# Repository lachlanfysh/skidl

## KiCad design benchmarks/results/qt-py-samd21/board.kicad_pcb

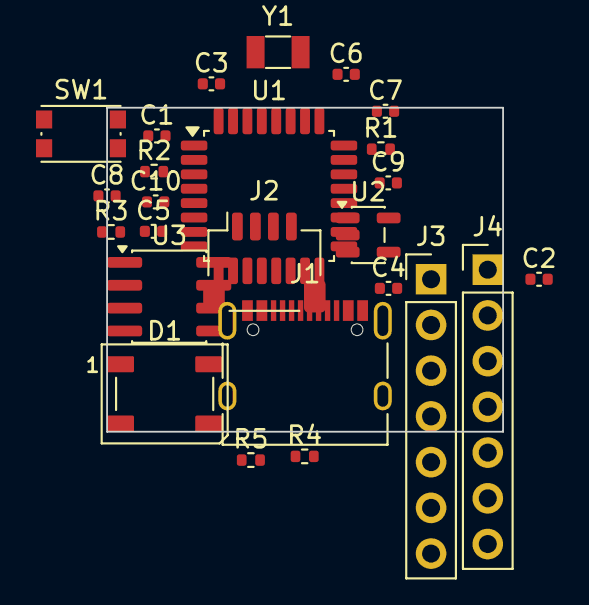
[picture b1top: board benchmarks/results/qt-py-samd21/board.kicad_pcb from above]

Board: 2 copper layers, 22.0 x 18.0 mm, 25 parts (0 on the bottom side), 25 nets, no tracks yet.

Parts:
C1, C2, C3: 1uF; C_0402_1005Metric
C4, C5, C8, C9, C10: 100nF; C_0402_1005Metric
C6, C7: 6.8pF; C_0402_1005Metric
D1: WS2812B; LED_WS2812B_PLCC4_5.0x5.0mm_P3.2mm
J1: USB_C; USB_C_Receptacle_XKB_U262-16XN-4BVC11
J2: Conn_01x04; JST_SH_SM04B-SRSS-TB_1x04-1MP_P1.00mm_Horizontal
J3, J4: Conn_01x07; PinHeader_1x07_P2.54mm_Vertical
R1, R2: 5.1K; R_0402_1005Metric
R3, R4, R5: 10K; R_0402_1005Metric
SW1: SW_Push; SW_Push_1P1T_NO_CK_KMR2
U1: ATSAMD21E18A-A; TQFP-32_7x7mm_P0.8mm
U2: AP2112K-3.3; SOT-23-5
U3: GD25Q16; SOIC-8_3.9x4.9mm_P1.27mm
Y1: 32.768kHz; Crystal_SMD_3215-2Pin_3.2x1.5mm

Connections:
+3V3: C2.1, C4.1, C5.1, C9.1, C10.1, D1.1, J2.2, J3.1, R3.1, R4.1, R5.1, U1.9, U1.30, U2.5, U3.3, U3.7, U3.8
A0_D0: J3.3, U1.3
A1_D1: J3.4, U1.4
A2_D2: J3.5, U1.13
A3_D3: J3.6, U1.14
FLASH_CS: U1.8, U3.1
FLASH_MISO: U1.7, U3.2
FLASH_MOSI: U1.5, U3.5
FLASH_SCK: U1.6, U3.6
GND: C1.2, C2.2, C3.2, C4.2, C5.2, C6.2, C7.2, C8.2, C9.2, C10.2, D1.3, J1.A1, J1.A12, J1.B1, J1.B12, J1.S1, J2.1, J3.2, R1.2, R2.2, SW1.2, U1.10, U1.28, U2.2, U3.4
MISO_D9: J4.3, U1.12
MOSI_D10: J4.4, U1.15
unnamed: J1.A5, R1.1
unnamed: J1.B5, R2.1
NEOPIXEL: D1.4, U1.25
SCK_D8: J4.2, U1.11
SCL: J2.4, J4.1, J4.6, R5.2, U1.18
SDA: J2.3, J3.7, J4.5, R4.2, U1.17
USB_D+: J1.A6, J1.B6, U1.24
USB_D-: J1.A7, J1.B7, U1.23
VBUS: C1.1, J1.A4, J1.A9, J1.B4, J1.B9, U2.1, U2.3
VDDCORE: C3.1, U1.29
XIN32: C6.1, U1.1, Y1.1
XOUT32: C7.1, U1.2, Y1.2
~RESET: C8.1, R3.2, SW1.1, U1.26

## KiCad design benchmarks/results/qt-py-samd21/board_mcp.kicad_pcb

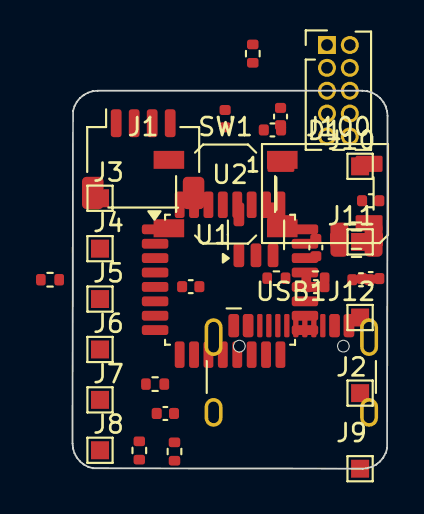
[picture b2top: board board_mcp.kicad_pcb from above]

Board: 2 copper layers, 17.5 x 21.0 mm, 37 parts (0 on the bottom side), 24 nets, no tracks yet.

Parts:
C1, C4, C5, C6, C7, C9, C10: 100nF; C_0402_1005Metric
C2, C3, C8: 1uF; C_0402_1005Metric
C11, C12: 10uF; C_0805_2012Metric
D1: WS2812B; LED_WS2812B_PLCC4_5.0x5.0mm_P3.2mm
J1: Conn_01x04; JST_SH_SM04B-SRSS-TB_1x04-1MP_P1.00mm_Horizontal
J2: 3V3; TestPoint_Pad_1.0x1.0mm
J3: GND; TestPoint_Pad_1.0x1.0mm
J4: A0; TestPoint_Pad_1.0x1.0mm
J5: A1; TestPoint_Pad_1.0x1.0mm
J6: A2; TestPoint_Pad_1.0x1.0mm
J7: A3; TestPoint_Pad_1.0x1.0mm
J8: A6; TestPoint_Pad_1.0x1.0mm
J9: A7; TestPoint_Pad_1.0x1.0mm
J10: A8; TestPoint_Pad_1.0x1.0mm
J11: A9; TestPoint_Pad_1.0x1.0mm
J12: A10; TestPoint_Pad_1.0x1.0mm
J100: SWD; PinHeader_2x05_P1.27mm_Vertical
R1, R2: 5.1k; R_0402_1005Metric
R3, R7: 10k; R_0402_1005Metric
R4: 300; R_0402_1005Metric
R5, R6: 4.7k; R_0402_1005Metric
SW1: SW_Push; SW_SPST_TL3342
U1: AP2112K-3.3; SOT-23-5
U2: ATSAMD21E18A-AU; TQFP-32_7x7mm_P0.8mm
USB1: TYPE-C 16PIN 2MD; USB_C_Receptacle_HCTL_HC-TYPE-C-16P-01A

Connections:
+3V3: C3.1, C4.1, C5.1, C6.1, C7.1, C8.1, C10.1, C11.1, D1.1, J1.2, J2.1, J100.1, R3.1, R5.1, R6.1, R7.1, U1.5, U2.9, U2.29, U2.30
A0: J4.1, U2.3
A1: J5.1, U2.5
A2: J6.1, U2.13
A3: J7.1, U2.11
A6: J8.1, U2.7
A7: J9.1, U2.12
A8: J10.1, U2.15
A9: J11.1, U2.16
A10: J12.1, U2.17
BOOT_N: R7.2, SW1.1, U2.8
GND: C1.2, C2.2, C3.2, C4.2, C5.2, C6.2, C7.2, C8.2, C9.2, C10.2, C11.2, C12.2, D1.3, J1.1, J3.1, J100.3, J100.5, J100.9, R1.2, R2.2, SW1.2, U1.2, U2.10, U2.28, USB1.A8, USB1.B8
NEOPIXEL_DIN: R4.1, U2.14
NEO_DIN_INT: D1.4, R4.2
RESET_N: C9.1, R3.2, U2.26
SCL: J1.4, R6.2, U2.22
SDA: J1.3, R5.2, U2.21
SWCLK: J100.4, U2.31
SWDIO: J100.2, U2.32
USB_CC1: R1.1, USB1.A5
USB_CC2: R2.1, USB1.B5
USB_DM: U2.24, USB1.A7, USB1.B7
USB_DP: U2.23, USB1.A6, USB1.B6
VBUS: C1.1, C2.1, C12.1, U1.1, U1.3

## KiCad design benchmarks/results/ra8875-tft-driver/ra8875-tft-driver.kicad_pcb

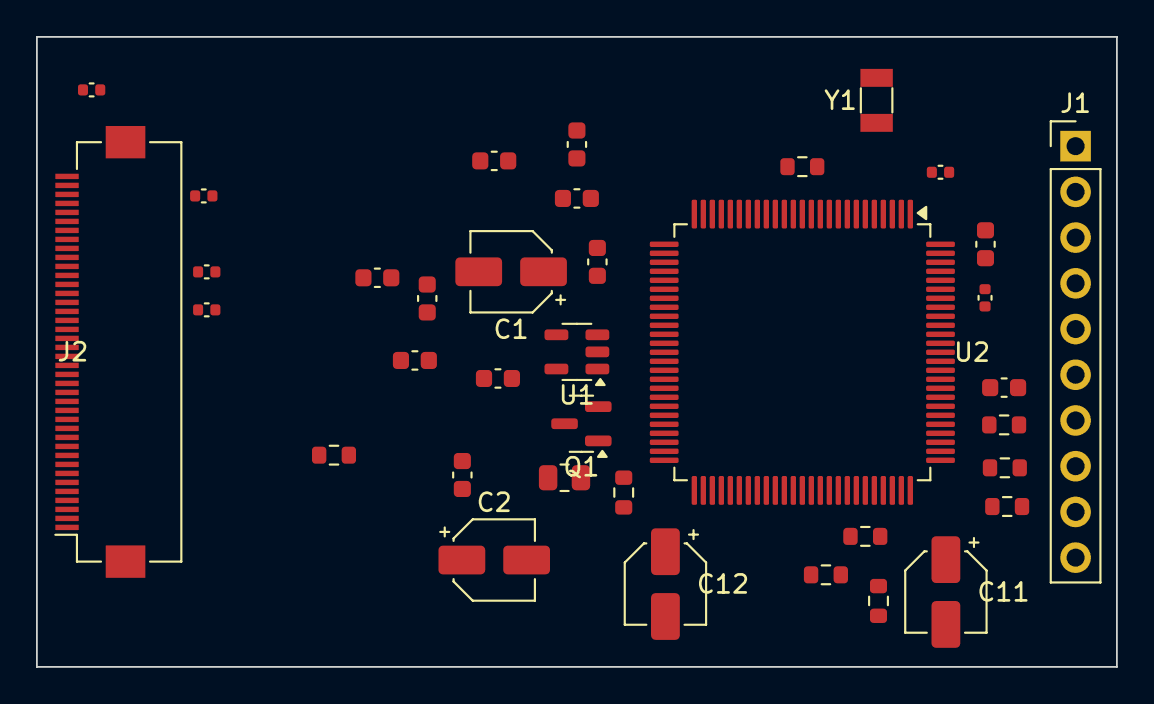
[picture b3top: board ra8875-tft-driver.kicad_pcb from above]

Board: 2 copper layers, 60.0 x 35.0 mm, 37 parts (0 on the bottom side), 43 nets, no tracks yet.

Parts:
C1, C2, C11, C12: 10uF; CP_Elec_4x5.4
C3, C4, C5, C6, C7, C8, C9, C10, C16, C21: 100nF; C_0603_1608Metric
C13: 1uF; C_0603_1608Metric
C14, C15: 18pF; C_0402_1005Metric
C17, C18, C19, C20: 100pF; C_0402_1005Metric
J1: SPI_HDR; PinHeader_1x10_P2.54mm_Vertical
J2: TFT_FPC_40P; Hirose_FH12-40S-0.5SH_1x40-1MP_P0.50mm_Horizontal
Q1: BSS138; SOT-23
R1, R2, R3, R4: 10K; R_0603_1608Metric
R5, R6, R7, R8: 1K; R_0603_1608Metric
R9: 100K; R_0603_1608Metric
R10: 10R; R_0805_2012Metric
U1: AP2112K-3.3; SOT-23-5
U2: RA8875DBXG; LQFP-100_14x14mm_P0.5mm
Y1: 20MHz; Crystal_SMD_3215-2Pin_3.2x1.5mm

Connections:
+3V3: C2.1, C3.1, C4.1, C5.1, C6.1, C7.1, C8.1, C9.1, C10.1, C11.1, C12.1, J1.2, J2.3, J2.37, R1.1, R2.1, R3.1, R4.1, R10.1, U1.5, U2.8, U2.10, U2.22, U2.37, U2.54, U2.67, U2.82, U2.96
BL_DRIVE: J2.38, Q1.3, R10.2
BL_PWM: Q1.1, R9.1, U2.78
DB0: J2.4, U2.39
DB1: J2.5, U2.40
DB2: J2.6, U2.41
DB3: J2.7, U2.42
DB4: J2.8, U2.43
DB5: J2.9, U2.44
DB6: J2.10, U2.45
DB7: J2.11, U2.46
DB8: J2.12, U2.47
DB9: J2.13, U2.48
DB10: J2.14, U2.49
DB11: J2.15, U2.50
DB12: J2.16, U2.51
DB13: J2.17, U2.52
DB14: J2.18, U2.53
DB15: J2.19, U2.56
DE: J2.24, U2.35
GND: C1.2, C2.2, C3.2, C4.2, C5.2, C6.2, C7.2, C8.2, C9.2, C10.2, C11.2, C12.2, C13.2, C14.2, C15.2, C16.2, C17.2, C18.2, C19.2, C20.2, C21.2, J1.3, J2.1, J2.2, J2.20, J2.21, J2.26, J2.27, J2.28, J2.29, J2.34, J2.35, J2.36, J2.39, J2.40, Q1.2, R9.2, U1.2, U2.9, U2.23, U2.38, U2.55, U2.68, U2.83, U2.92, U2.93, U2.97
HSYNC: J2.22, U2.33
INT: J1.8, R2.2, U2.75
PCLK: J2.25, U2.36
SPI_CS: J1.7, R1.2, U2.74
SPI_MISO: J1.6, U2.73
SPI_MOSI: J1.5, U2.72
SPI_SCK: J1.4, U2.71
TP_XN: R6.1, U2.85
TP_XN_F: C18.1, J2.31, R6.2
TP_XP: R5.1, U2.84
TP_XP_F: C17.1, J2.30, R5.2
TP_YN: R8.1, U2.87
TP_YN_F: C20.1, J2.33, R8.2
TP_YP: R7.1, U2.86
TP_YP_F: C19.1, J2.32, R7.2
VDDCORE: C13.1, U2.100
VIN: C1.1, C21.1, J1.1, U1.1, U1.3
VSYNC: J2.23, U2.34
WAIT: J1.10, R3.2, U2.76
XI: C14.1, U2.98, Y1.1
XO: C15.1, U2.99, Y1.2
nRESET: C16.1, J1.9, R4.2, U2.77

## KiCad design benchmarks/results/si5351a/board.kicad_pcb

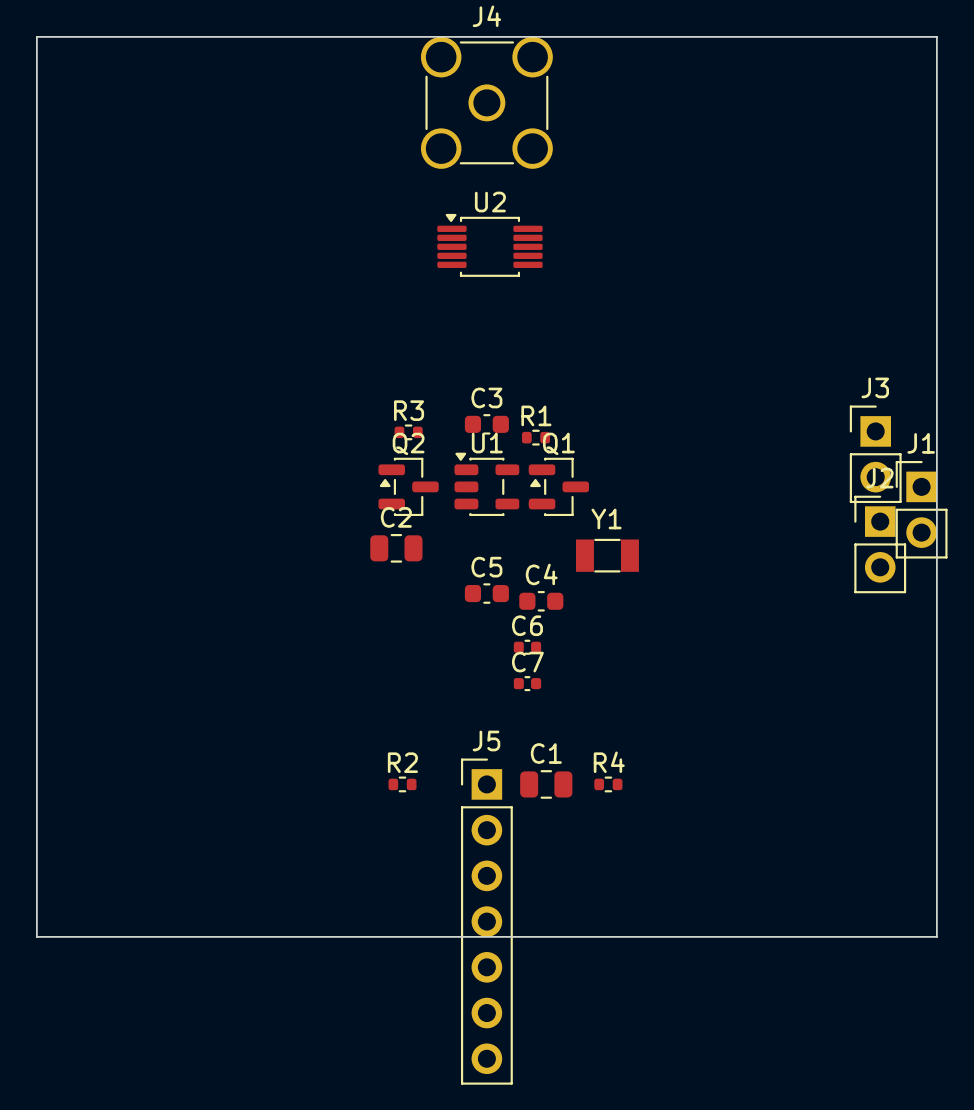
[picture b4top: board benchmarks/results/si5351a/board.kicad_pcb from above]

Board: 2 copper layers, 50.0 x 50.0 mm, 21 parts (0 on the bottom side), 13 nets, no tracks yet.

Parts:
C1, C2: 10uF; C_0805_2012Metric
C3, C4, C5: 100nF; C_0603_1608Metric
C6, C7: 10pF; C_0402_1005Metric
J1, J2, J3: Conn_01x02; PinHeader_1x02_P2.54mm_Vertical
J4: Conn_01x01; SMA_Amphenol_132134-11_Vertical
J5: Conn_01x07; PinHeader_1x07_P2.54mm_Vertical
Q1, Q2: BSS138; SOT-23
R1, R2, R3, R4: 10K; R_0402_1005Metric
U1: AP2112K-3.3; SOT-23-5
U2: Si5351A; MSOP-10_3x3mm_P0.5mm
Y1: 25MHz; Crystal_SMD_3215-2Pin_3.2x1.5mm

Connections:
+3V3: C2.1, C3.1, C4.1, C5.1, Q1.1, Q2.1, R1.1, R3.1, U1.5, U2.3, U2.8
CLK0: J1.1, J4.1, U2.5
CLK1: J2.1, U2.6
CLK2: J3.1, U2.7
GND: C1.2, C2.2, C3.2, C4.2, C5.2, C6.2, C7.2, J1.2, J2.2, J3.2, J5.2, J5.6, U1.2, U2.4
unnamed: C6.1, U2.10, Y1.1
unnamed: C7.1, U2.9, Y1.2
SCL: J5.3, Q2.3, R4.2
SCL_3V: Q2.2, R3.2, U2.2
SDA: J5.4, Q1.3, R2.2
SDA_3V: Q1.2, R1.2, U2.1
VIN: C1.1, J5.1, J5.7, U1.1, U1.3
VIO: J5.5, R2.1, R4.1

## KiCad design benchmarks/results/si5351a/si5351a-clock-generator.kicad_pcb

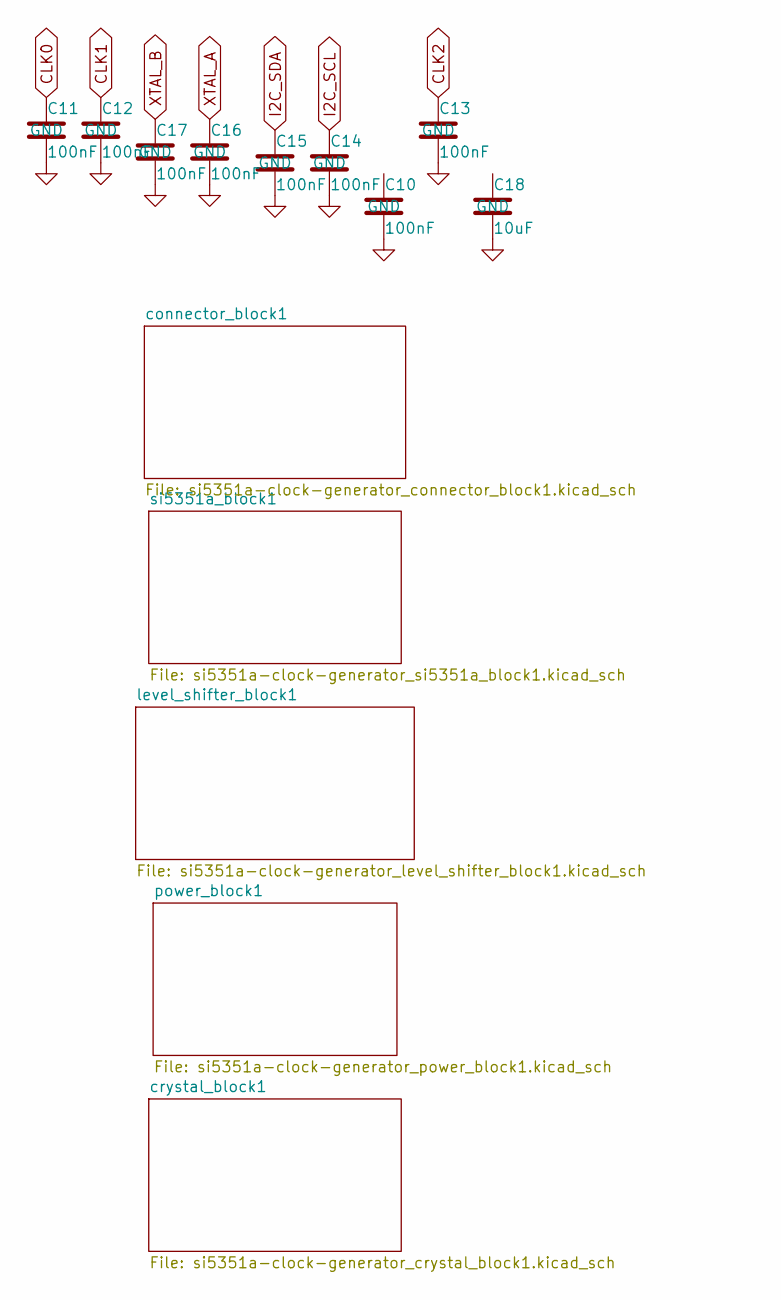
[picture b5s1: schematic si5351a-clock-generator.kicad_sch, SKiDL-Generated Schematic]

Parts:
C10, C11, C12, C13, C14, C15, C16, C17: 100nF; C_0603_1608Metric
C18: 10uF; C_0805_2012Metric

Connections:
CLK0: C11.1; also elsewhere on the board
CLK1: C12.1; also elsewhere on the board
CLK2: C13.1; also elsewhere on the board
GND: C10.2, C11.2, C12.2, C13.2, C14.2, C15.2, C16.2, C17.2, C18.2; also elsewhere on the board
I2C_SCL: C14.1; also elsewhere on the board
I2C_SDA: C15.1; also elsewhere on the board
XTAL_A: C16.1; also elsewhere on the board
XTAL_B: C17.1; also elsewhere on the board

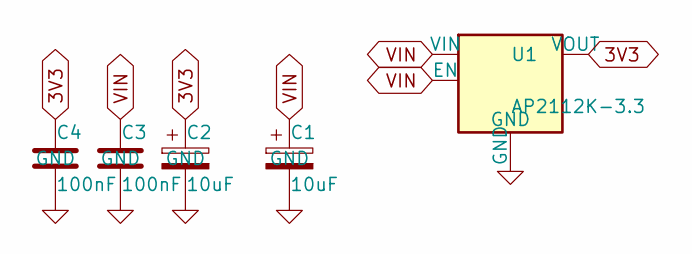
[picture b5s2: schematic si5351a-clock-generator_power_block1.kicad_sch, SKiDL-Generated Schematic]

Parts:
C1, C2: 10uF; C_0805_2012Metric
C3, C4: 100nF; C_0603_1608Metric
U1: AP2112K-3.3; SOT-23-5

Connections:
3V3: C2.1, C4.1, U1.5 (VOUT); also elsewhere on the board
GND: C1.2, C2.2, C3.2, C4.2, U1.2 (GND); also elsewhere on the board
VIN: C1.1, C3.1, U1.1 (VIN), U1.3 (EN); also elsewhere on the board

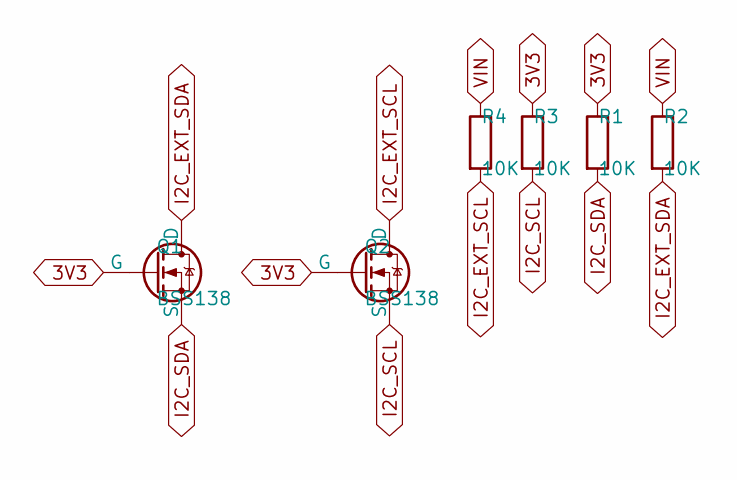
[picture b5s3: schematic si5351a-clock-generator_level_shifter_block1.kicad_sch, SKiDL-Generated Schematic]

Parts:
Q1, Q2: BSS138; SOT-23
R1, R2, R3, R4: 10K; R_0603_1608Metric

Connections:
3V3: Q1.1 (G), Q2.1 (G), R1.1, R3.1; also elsewhere on the board
I2C_EXT_SCL: Q2.3 (D), R4.2; also elsewhere on the board
I2C_EXT_SDA: Q1.3 (D), R2.2; also elsewhere on the board
I2C_SCL: Q2.2 (S), R3.2; also elsewhere on the board
I2C_SDA: Q1.2 (S), R1.2; also elsewhere on the board
VIN: R2.1, R4.1; also elsewhere on the board

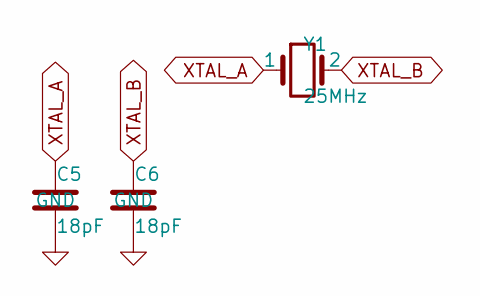
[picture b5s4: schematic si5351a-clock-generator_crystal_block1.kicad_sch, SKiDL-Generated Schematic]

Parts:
C5, C6: 18pF; C_0402_1005Metric
Y1: 25MHz; Crystal_SMD_3225-4Pin_3.2x2.5mm

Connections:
GND: C5.2, C6.2; also elsewhere on the board
XTAL_A: C5.1, Y1.1; also elsewhere on the board
XTAL_B: C6.1, Y1.2; also elsewhere on the board

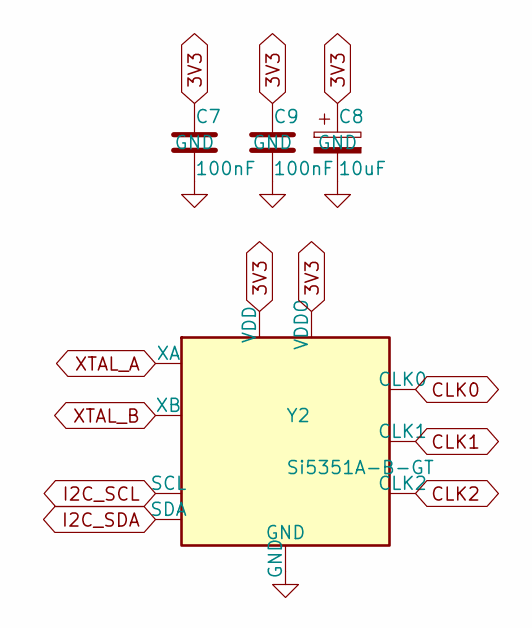
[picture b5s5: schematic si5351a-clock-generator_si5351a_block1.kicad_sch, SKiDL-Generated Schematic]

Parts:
C7, C9: 100nF; C_0402_1005Metric
C8: 10uF; C_0805_2012Metric
Y2: Si5351A-B-GT; MSOP-10_3x3mm_P0.5mm

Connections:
3V3: C7.1, C8.1, C9.1, Y2.1 (VDD), Y2.7 (VDDO); also elsewhere on the board
CLK0: Y2.10 (CLK0); also elsewhere on the board
CLK1: Y2.9 (CLK1); also elsewhere on the board
CLK2: Y2.6 (CLK2); also elsewhere on the board
GND: C7.2, C8.2, C9.2, Y2.8 (GND); also elsewhere on the board
I2C_SCL: Y2.4 (SCL); also elsewhere on the board
I2C_SDA: Y2.5 (SDA); also elsewhere on the board
XTAL_A: Y2.2 (XA); also elsewhere on the board
XTAL_B: Y2.3 (XB); also elsewhere on the board

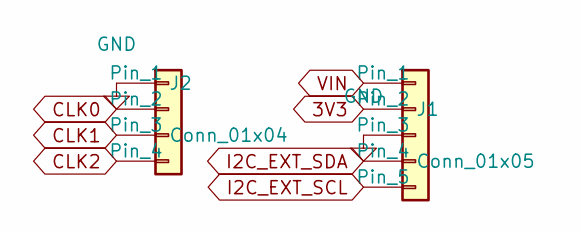
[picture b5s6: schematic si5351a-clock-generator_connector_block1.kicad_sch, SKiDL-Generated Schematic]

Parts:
J1: Conn_01x05; PinHeader_1x05_P2.54mm_Vertical
J2: Conn_01x04; PinHeader_1x04_P2.54mm_Vertical

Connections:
3V3: J1.2; also elsewhere on the board
CLK0: J2.2; also elsewhere on the board
CLK1: J2.3; also elsewhere on the board
CLK2: J2.4; also elsewhere on the board
GND: J1.3, J2.1; also elsewhere on the board
I2C_EXT_SCL: J1.5; also elsewhere on the board
I2C_EXT_SDA: J1.4; also elsewhere on the board
VIN: J1.1; also elsewhere on the board

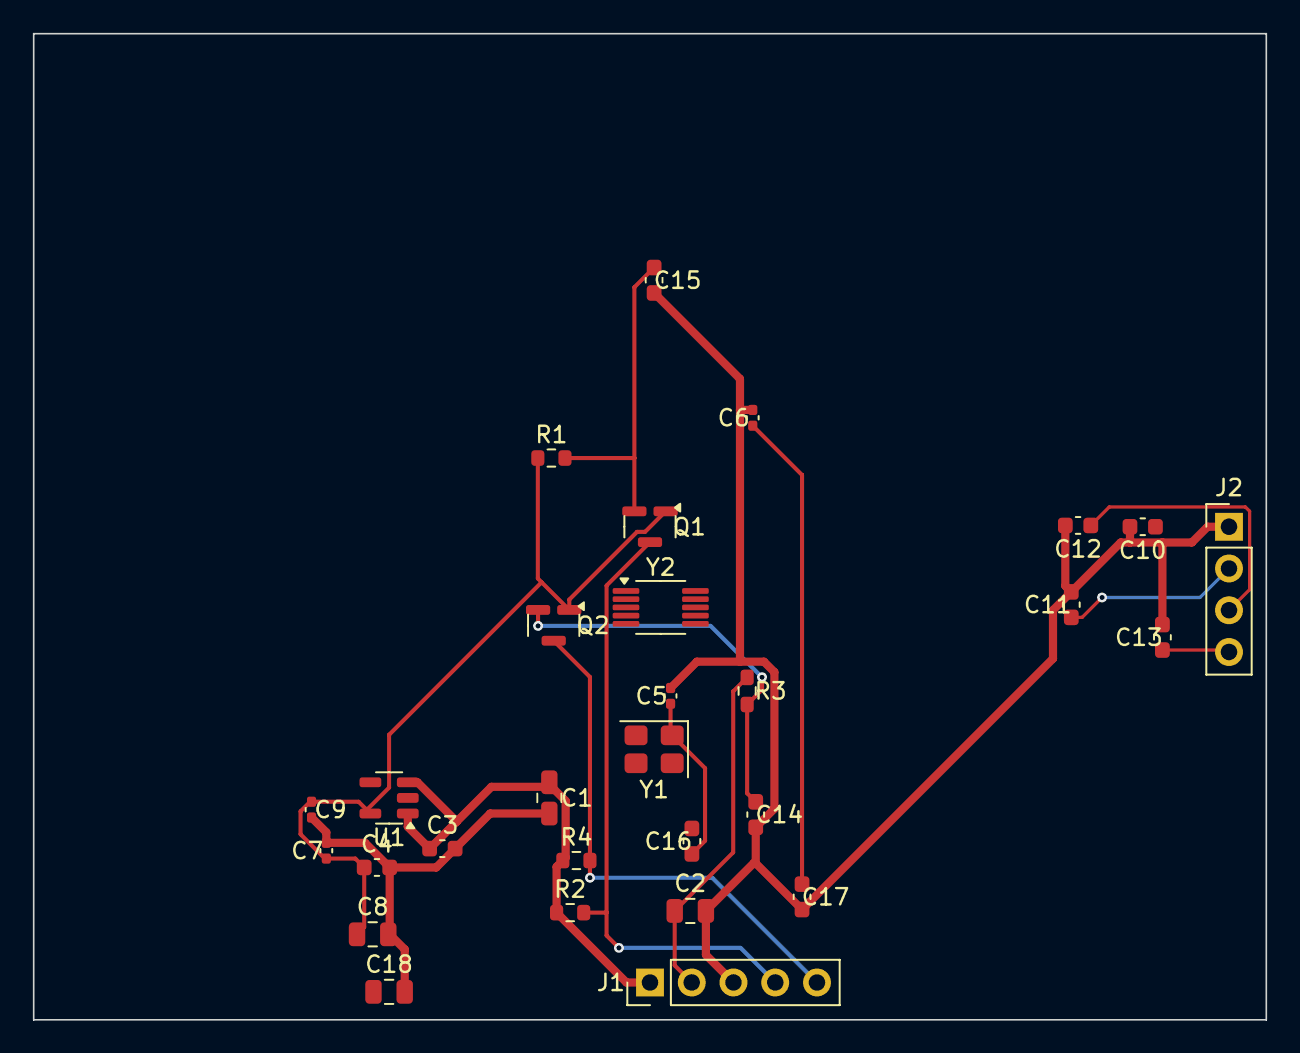
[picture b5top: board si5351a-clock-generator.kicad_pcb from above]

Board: 2 copper layers, 75.0 x 60.0 mm, 29 parts (0 on the bottom side), 12 nets.

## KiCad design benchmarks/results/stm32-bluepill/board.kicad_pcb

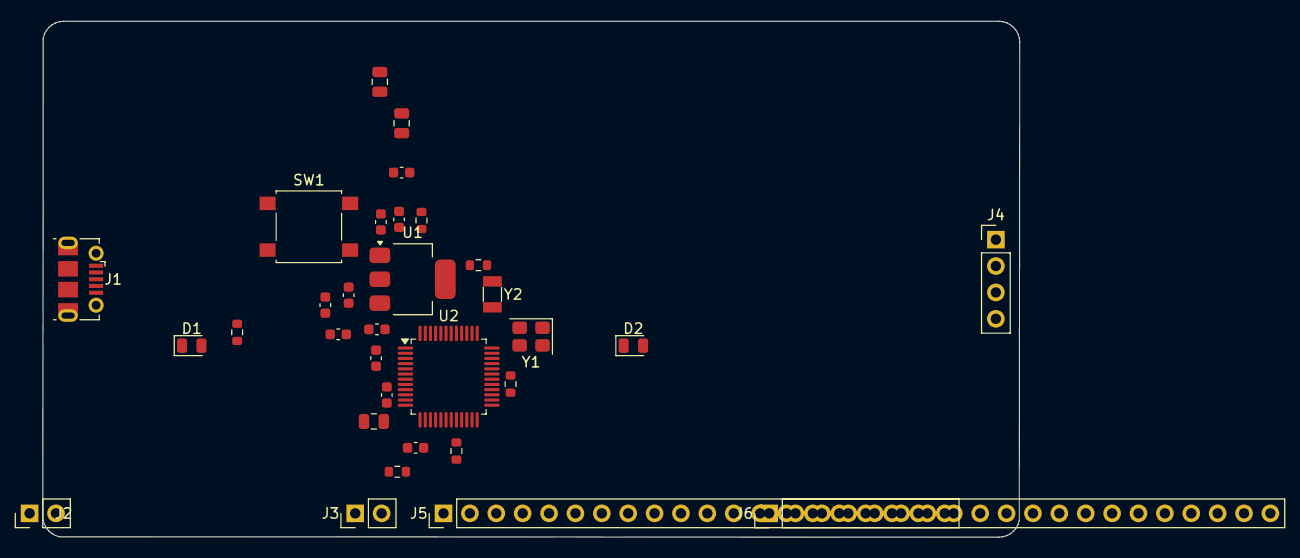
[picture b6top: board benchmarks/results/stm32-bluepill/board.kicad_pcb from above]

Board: 2 copper layers, 94.1 x 49.7 mm, 32 parts (0 on the bottom side), 44 nets, no tracks yet.

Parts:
C1, C2: 10uF; C_0805_2012Metric
C3, C4, C5, C6, C7, C13: 100nF; C_0603_1608Metric
C8: 4u7; C_0805_2012Metric
C9, C10: 22pF; C_0603_1608Metric
C11, C12: 12pF; C_0603_1608Metric
D1: PWR_LED; LED_0805_2012Metric
D2: USER_LED; LED_0805_2012Metric
J1: USB_B_Micro; USB_Micro-B_Molex-105017-0001
J2, J3: Conn_01x02_Pin; PinHeader_1x02_P2.54mm_Vertical
J4: Conn_01x04_Pin; PinHeader_1x04_P2.54mm_Vertical
J5, J6: Conn_01x20_Pin; PinHeader_1x20_P2.54mm_Vertical
R1: 1k5; R_0603_1608Metric
R2, R3: 1k; R_0603_1608Metric
R4, R5, R6: 10k; R_0603_1608Metric
SW1: SW_Push; SW_SPST_B3S-1000
U1: AMS1117-3.3; SOT-223-3_TabPin2
U2: STM32F103C8Tx; LQFP-48_7x7mm_P0.5mm
Y1: Crystal_GND23; Crystal_SMD_3225-4Pin_3.2x2.5mm
Y2: Crystal; Crystal_SMD_3215-2Pin_3.2x1.5mm

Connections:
+3.3V: C2.1, C3.1, C4.1, C5.1, C6.1, C7.1, C8.1, D2.2, J2.2, J3.2, J4.1, J5.12, J5.20, J6.16, J6.17, R1.1, R2.1, R4.1, U1.2, U2.1, U2.9, U2.24, U2.36, U2.48
GND: C1.2, C2.2, C3.2, C4.2, C5.2, C6.2, C7.2, C8.2, C9.2, C10.2, C11.2, C12.2, C13.2, D1.1, J1.4, J1.5, J1.6, J4.4, J5.13, J5.19, J6.14, J6.15, R5.1, R6.1, SW1.2, U1.1, U2.8, U2.23, U2.35, U2.47, Y1.2, Y1.3
unnamed: J1.3, R1.2, U2.33
unnamed: D1.2, R2.2
unnamed: J1.2, U2.32
unnamed: D2.1, R3.1
unnamed: C9.1, U2.5, Y1.1
unnamed: C10.1, U2.6, Y1.4
unnamed: C11.1, U2.3, Y2.1
unnamed: C12.1, U2.4, Y2.2
unnamed: J2.1, R5.2, U2.44
unnamed: J3.1, R6.2, U2.20
unnamed: J4.2, J6.18, U2.34
unnamed: J4.3, J6.19, U2.37
NRST_HDR: C13.1, J6.13, R4.2, SW1.1, U2.7
PA0_HDR: J5.1, U2.10
PA1_HDR: J5.2, U2.11
PA2_HDR: J5.3, U2.12
PA3_HDR: J5.4, U2.13
PA4_HDR: J5.5, U2.14
PA5_HDR: J5.6, U2.15
PA6_HDR: J5.7, U2.16
PA7_HDR: J5.8, U2.17
PA8_HDR: J5.9, U2.29
PA9_HDR: J5.10, U2.30
PA10_HDR: J5.11, U2.31
PA15_HDR: J5.14, U2.38
PB0_HDR: J5.15, U2.18
PB1_HDR: J5.16, U2.19
PB3_HDR: J6.5, J6.20, U2.39
PB4_HDR: J6.6, U2.40
PB5_HDR: J6.7, U2.41
PB6_HDR: J6.8, U2.42
PB7_HDR: J6.9, U2.43
PB8_HDR: J6.10, U2.45
PB9_HDR: J6.11, U2.46
PB10_HDR: J5.17, U2.21
PB11_HDR: J5.18, U2.22
PB12_HDR: J6.1, U2.25
PB13_HDR: J6.2, U2.26
PB14_HDR: J6.3, U2.27
PB15_HDR: J6.4, U2.28
PC13_HDR: J6.12, R3.2, U2.2
VBUS: C1.1, J1.1, U1.3

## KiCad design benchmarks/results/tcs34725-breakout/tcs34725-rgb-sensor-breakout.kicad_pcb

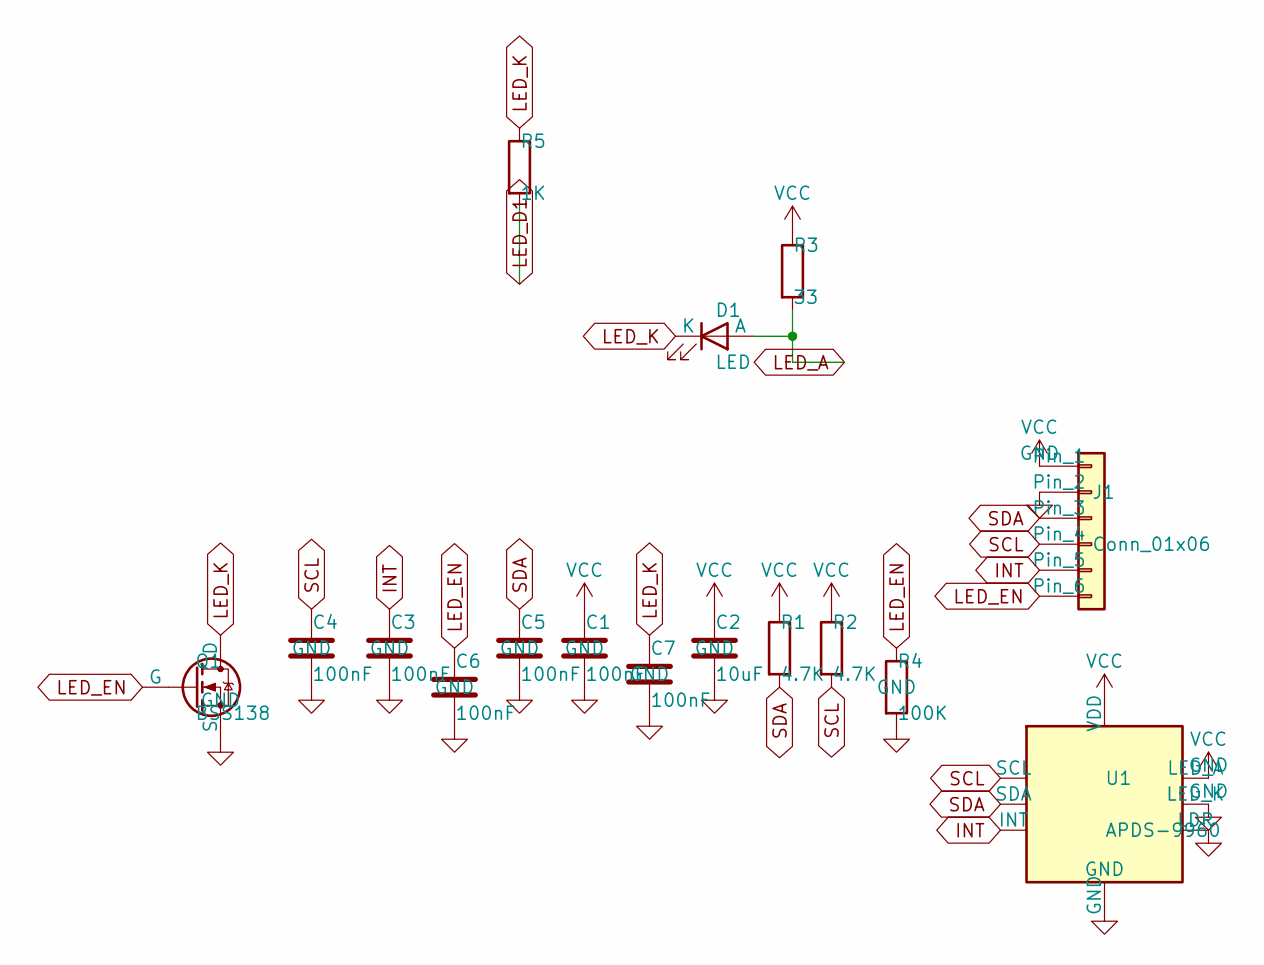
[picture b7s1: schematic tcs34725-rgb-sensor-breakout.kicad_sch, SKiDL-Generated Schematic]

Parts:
C1: 100nF; C_0402_1005Metric
C2: 10uF; C_0805_2012Metric
C3, C4, C5, C6, C7: 100nF; C_0603_1608Metric
D1: LED; LED_0402_1005Metric
J1: Conn_01x06; PinHeader_1x06_P2.54mm_Vertical
Q1: BSS138; SOT-23
R1, R2: 4.7K; R_0402_1005Metric
R3: 33; R_0402_1005Metric
R4: 100K; R_0402_1005Metric
R5: 1K; R_0603_1608Metric
U1: APDS-9960; Avago_APDS-9960

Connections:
GND: C1.2, C2.2, C3.2, C4.2, C5.2, C6.2, C7.2, J1.2, Q1.2 (S), R4.2, U1.3 (LDR), U1.4 (LED_K), U1.6 (GND)
INT: C3.1, J1.5, U1.2 (INT)
LED_A: D1.2 (A), R3.2
LED_D1: R5.2
LED_EN: C6.1, J1.6, Q1.1 (G), R4.1
LED_K: C7.1, D1.1 (K), Q1.3 (D), R5.1
SCL: C4.1, J1.4, R2.2, U1.7 (SCL)
SDA: C5.1, J1.3, R1.2, U1.1 (SDA)
VCC: C1.1, C2.1, J1.1, R1.1, R2.1, R3.1, U1.5 (LED_A), U1.8 (VDD)

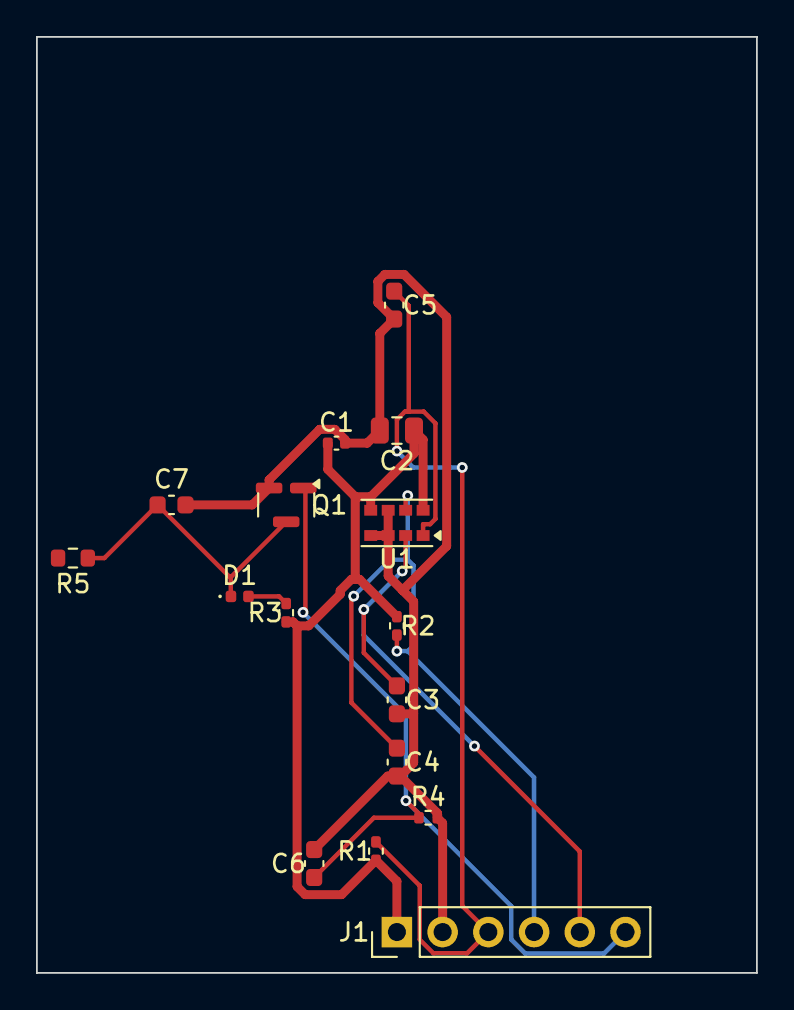
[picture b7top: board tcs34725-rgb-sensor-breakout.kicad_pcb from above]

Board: 2 copper layers, 40.0 x 52.0 mm, 16 parts (0 on the bottom side), 8 nets.

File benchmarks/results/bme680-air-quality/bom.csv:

Comment,Designator,Footprint,LCSC Part Number
Conn_01x06,J1,Connector_PinHeader_2.54mm:PinHeader_1x06_P2.54mm_Vertical,
AP2112K-3.3,U1,Package_TO_SOT_SMD:SOT-23-5,
1uF,C1,Capacitor_SMD:C_0603_1608Metric,
10uF,C2,Capacitor_SMD:C_0805_2012Metric,
100nF,C3,Capacitor_SMD:C_0603_1608Metric,
TXB0104D,U2,Package_SO:SOIC-14_3.9x8.7mm_P1.27mm,
100nF,C4,Capacitor_SMD:C_0603_1608Metric,
100nF,C5,Capacitor_SMD:C_0603_1608Metric,
BME680,U3,Package_LGA:Bosch_LGA-8_3x3mm_P0.8mm_ClockwisePinNumbering,
100nF,C6,Capacitor_SMD:C_0402_1005Metric,
100nF,C7,Capacitor_SMD:C_0402_1005Metric,
4.7K,R1,Resistor_SMD:R_0603_1608Metric,
4.7K,R2,Resistor_SMD:R_0603_1608Metric,
10K,R3,Resistor_SMD:R_0603_1608Metric,
10uF,C8,Capacitor_SMD:C_0805_2012Metric,

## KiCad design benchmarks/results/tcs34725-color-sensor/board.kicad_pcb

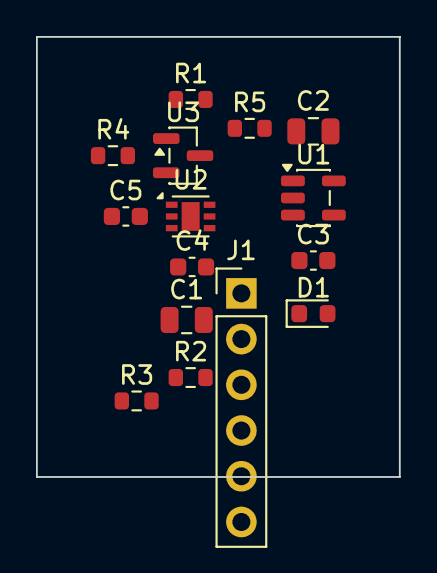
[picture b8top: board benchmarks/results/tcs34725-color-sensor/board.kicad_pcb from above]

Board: 2 copper layers, 20.2 x 24.4 mm, 15 parts (0 on the bottom side), 9 nets, no tracks yet.

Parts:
C1, C2: 10uF; C_0805_2012Metric
C3, C4: 100nF; C_0603_1608Metric
C5: 1uF; C_0603_1608Metric
D1: WHITE; LED_0603_1608Metric
J1: Conn_01x06; PinHeader_1x06_P2.54mm_Vertical
R1, R2: 4.7K; R_0603_1608Metric
R3: 10K; R_0603_1608Metric
R4: 100K; R_0603_1608Metric
R5: 68R; R_0603_1608Metric
U1: AP2112K-3.3; SOT-23-5
U2: TCS34725; DFN-6-1EP_2x2mm_P0.65mm_EP1x1.6mm
U3: BSS138; SOT-23

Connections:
+3V3: C2.1, C3.1, C4.1, C5.1, D1.1, R1.1, R2.1, R3.1, U1.5, U2.1
GND: C1.2, C2.2, C3.2, C4.2, C5.2, J1.2, R4.2, U1.2, U2.2, U2.7, U3.2
INT: J1.5, R3.2, U2.5
LED_DRV: J1.6, R4.1, U2.6, U3.1
unnamed: D1.2, R5.1
unnamed: R5.2, U3.3
SCL: J1.4, R2.2, U2.4
SDA: J1.3, R1.2, U2.3
VIN: C1.1, J1.1, U1.1, U1.3

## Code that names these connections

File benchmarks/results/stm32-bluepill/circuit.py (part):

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    c_bulk[2] += gnd

    # USB D+/D- on PA11/PA12
    usb_dm += u1["PA11"]
    usb_dp += u1["PA12"]

    # User LED on PC13 (active low — current sink)
    global net_pc13
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    h.edge_preference = "bottom"

    nets = [
        Net("PA0_HDR"),  Net("PA1_HDR"),  Net("PA2_HDR"),  Net("PA3_HDR"),
        Net("PA4_HDR"),  Net("PA5_HDR"),  Net("PA6_HDR"),  Net("PA7_HDR"),
        Net("PA8_HDR"),  Net("PA9_HDR"),  Net("PA10_HDR"),
        vcc, gnd,
        Net("PA15_HDR"),
        Net("PB0_HDR"),  Net("PB1_HDR"),
        Net("PB10_HDR"), Net("PB11_HDR"),
        gnd, vcc,
    ]
    for i, n in enumerate(nets, start=1):
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    h.edge_preference = "bottom"

    nets = [
        Net("PB12_HDR"), Net("PB13_HDR"), Net("PB14_HDR"), Net("PB15_HDR"),
        Net("PB3_HDR"),  Net("PB4_HDR"),  Net("PB5_HDR"),  Net("PB6_HDR"),
        Net("PB7_HDR"),  Net("PB8_HDR"),  Net("PB9_HDR"),
        Net("PC13_HDR"), Net("NRST_HDR"),
        gnd, gnd, vcc, vcc,
        net_swdio, net_swdclk, net_swo,
    ]
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    pb_pins["PB8"]  += nets[9];  pb_pins["PB9"]  += nets[10]
    net_pc13    += nets[11]
    net_nrst    += nets[12]
    # nets[4] is PB3_HDR; connect to net_swo (PB3 is SWO, already in MCU)
    net_swo     += nets[4]

gpio_header_a()
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
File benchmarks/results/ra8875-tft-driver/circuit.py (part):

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@subcircuit
def ra8875_controller(vdd, gnd_net, vddcore_net,
                      sck, mosi, miso, cs,
                      int_pin, rst_pin, wait_pin,
                      xi, xo,
                      db, hsync, vsync, de, pclk,
                      txp, txn, typ, tyn,
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                 Pin(num="74",  name="SCS",   func=Pin.types.INPUT),
                 # Control
                 Pin(num="75",  name="INT",   func=Pin.types.OUTPUT),
                 Pin(num="76",  name="WAIT",  func=Pin.types.OUTPUT),
                 Pin(num="77",  name="RESET", func=Pin.types.INPUT),
                 # Crystal
                 Pin(num="98",  name="XI",    func=Pin.types.INPUT),
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                 Pin(num="53",  name="DB14",  func=Pin.types.OUTPUT),
                 Pin(num="56",  name="DB15",  func=Pin.types.OUTPUT),
                 # TFT control
                 Pin(num="33",  name="HSYNC", func=Pin.types.OUTPUT),
                 Pin(num="34",  name="VSYNC", func=Pin.types.OUTPUT),
                 Pin(num="35",  name="DE",    func=Pin.types.OUTPUT),
                 Pin(num="36",  name="PCLK",  func=Pin.types.OUTPUT),
                 # Touch interface
                 Pin(num="84",  name="TP_XP", func=Pin.types.BIDIR),
                 Pin(num="85",  name="TP_XN", func=Pin.types.BIDIR),
                 Pin(num="86",  name="TP_YP", func=Pin.types.BIDIR),
                 Pin(num="87",  name="TP_YN", func=Pin.types.BIDIR),
                 # PWM backlight
                 Pin(num="78",  name="PWM1",  func=Pin.types.OUTPUT),
                 # Config pins
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
    # Control
    u["INT"]   += int_pin
    u["WAIT"]  += wait_pin
    u["RESET"] += rst_pin

    # Crystal
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# SPI Pull-ups and Reset RC
# ============================================================
@subcircuit
def spi_conditioning(vdd, gnd_net, cs, int_pin, rst_pin, wait_pin):
    for sig in [cs, int_pin, wait_pin]:
        r = Part("Device", "R", value="10K",
                 footprint="Resistor_SMD:R_0603_1608Metric")
        r[1] += vdd; r[2] += sig
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# ============================================================
@subcircuit
def spi_header(vin, v3v3_net, gnd_net, sck, mosi, miso, cs,
               int_pin, rst_pin, wait_pin):
    j = Part("Connector_Generic", "Conn_01x10",
             footprint="Connector_PinHeader_2.54mm:PinHeader_1x10_P2.54mm_Vertical",
             value="SPI_HDR")
    j[1]  += vin;      j[2]  += v3v3_net; j[3]  += gnd_net
    j[4]  += sck;      j[5]  += mosi;     j[6]  += miso
    j[7]  += cs;       j[8]  += int_pin;  j[9]  += rst_pin
    j[10] += wait_pin


# ============================================================
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
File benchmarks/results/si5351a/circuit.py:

"""
Si5351A I2C clock generator breakout board.
- Si5351A-B-GM QFN-20: 3 independent outputs, 8kHz-150MHz
- 25MHz crystal reference (SMD 3225-4pin)
- 3.3V LDO from 5V VIN (AMS1117-3.3)
- I2C interface with 4.7k pull-ups
- CLK0/CLK1/CLK2 available on 2.54mm pin headers
"""

from skidl import *

# Power rails
vcc3v3 = Net("3V3"); vcc3v3.drive = POWER
vcc5v = Net("VIN"); vcc5v.drive = POWER
gnd = Net("GND"); gnd.drive = POWER

# I2C nets
i2c_sda = Net("SDA")
i2c_scl = Net("SCL")

# Clock output nets
clk0 = Net("CLK0")
clk1 = Net("CLK1")
clk2 = Net("CLK2")

# Crystal nets
xa = Net("XA")
xb = Net("XB")


@subcircuit
def si5351a_block(vcc3v3, gnd, sda, scl, clk0, clk1, clk2, xa, xb):
    """Si5351A clock generator IC with decoupling."""
    u1 = Part("Oscillator", "Si5351A-B-GM",
              footprint="Package_DFN_QFN:QFN-20-1EP_4x4mm_P0.5mm_EP2.7x2.7mm",
              value="Si5351A")

    vcc3v3 += u1["VDD"], u1["VDDOA"], u1["VDDOB"], u1["VDDOC"], u1["VDDOD"]
    gnd += u1["GND"]
    u1["XA"] += xa
    u1["XB"] += xb
    u1["SDA"] += sda
    u1["SCL"] += scl
    u1["A0"] += gnd        # I2C addr 0x60
    u1["OEB"] += gnd       # Enable all outputs
    u1["SSEN"] += gnd      # No spread spectrum
    u1["CLK0"] += clk0
    u1["CLK1"] += clk1
    u1["CLK2"] += clk2
    # Unused outputs tied to GND (ERC warnings expected per design brief)
    gnd += u1["CLK3"], u1["CLK4"], u1["CLK5"], u1["CLK6"], u1["CLK7"]

    # VDD core decoupling (0603 for easier routing)
    c1 = Part("Device", "C", value="100nF",
              footprint="Capacitor_SMD:C_0603_1608Metric")
    c1[1] += vcc3v3; c1[2] += gnd

    # Shared output supply decoupling (2 caps for VDDOA-D cluster)
    c2 = Part("Device", "C", value="100nF",
              footprint="Capacitor_SMD:C_0603_1608Metric")
    c2[1] += vcc3v3; c2[2] += gnd

    c3 = Part("Device", "C", value="100nF",
              footprint="Capacitor_SMD:C_0603_1608Metric")
    c3[1] += vcc3v3; c3[2] += gnd

    # 3V3 bulk
    cb = Part("Device", "C", value="10uF",
              footprint="Capacitor_SMD:C_0805_2012Metric")
    cb[1] += vcc3v3; cb[2] += gnd


@subcircuit
def crystal_block(gnd, xa, xb):
    """25MHz crystal with load capacitors."""
    y1 = Part("Device", "Crystal_GND23",
              footprint="Crystal:Crystal_SMD_3225-4Pin_3.2x2.5mm",
              value="25MHz")
    y1[1] += xa
    y1[4] += xb
    y1[2] += gnd
    y1[3] += gnd

    c_xa = Part("Device", "C", value="18pF",
                footprint="Capacitor_SMD:C_0402_1005Metric")
    c_xb = Part("Device", "C", value="18pF",
                footprint="Capacitor_SMD:C_0402_1005Metric")
    c_xa[1] += xa; c_xa[2] += gnd
    c_xb[1] += xb; c_xb[2] += gnd


@subcircuit
def power_block(vin, vcc3v3, gnd):
    """AMS1117-3.3 LDO with input/output capacitors."""
    u2 = Part("Regulator_Linear", "AMS1117-3.3",
              footprint="Package_TO_SOT_SMD:SOT-223-3_TabPin2",
              value="AMS1117-3.3")
    vin += u2["VI"]
    gnd += u2["GND"]
    vcc3v3 += u2["VO"]

    c_in = Part("Device", "C", value="10uF",
                footprint="Capacitor_SMD:C_0805_2012Metric")
    c_in[1] += vin; c_in[2] += gnd

    c_out = Part("Device", "C", value="10uF",
                 footprint="Capacitor_SMD:C_0805_2012Metric")
    c_out[1] += vcc3v3; c_out[2] += gnd


@subcircuit
def connector_block(vin, vcc3v3, gnd, sda, scl, clk0, clk1, clk2):
    """Headers: power/I2C on left, clock outputs on right."""
    # I2C pull-ups to 3V3
    r_sda = Part("Device", "R", value="4.7k",
                 footprint="Resistor_SMD:R_0603_1608Metric")
    r_scl = Part("Device", "R", value="4.7k",
                 footprint="Resistor_SMD:R_0603_1608Metric")
    r_sda[1] += vcc3v3; r_sda[2] += sda
    r_scl[1] += vcc3v3; r_scl[2] += scl

    # Power + I2C header: VIN, GND, SDA, SCL
    j1 = Part("Connector", "Conn_01x04_Pin",
              footprint="Connector_PinHeader_2.54mm:PinHeader_1x04_P2.54mm_Vertical",
              value="PWR+I2C")
    j1.edge_preference = "left"
    j1[1] += vin
    j1[2] += gnd
    j1[3] += sda
    j1[4] += scl

    # CLK output headers (signal + GND per output)
    j2 = Part("Connector", "Conn_01x02_Pin",
              footprint="Connector_PinHeader_2.54mm:PinHeader_1x02_P2.54mm_Vertical",
              value="CLK0")
    j2.edge_preference = "right"
    j2[1] += clk0; j2[2] += gnd

    j3 = Part("Connector", "Conn_01x02_Pin",
              footprint="Connector_PinHeader_2.54mm:PinHeader_1x02_P2.54mm_Vertical",
              value="CLK1")
    j3.edge_preference = "right"
    j3[1] += clk1; j3[2] += gnd

    j4 = Part("Connector", "Conn_01x02_Pin",
              footprint="Connector_PinHeader_2.54mm:PinHeader_1x02_P2.54mm_Vertical",
              value="CLK2")
    j4.edge_preference = "right"
    j4[1] += clk2; j4[2] += gnd


# Instantiate blocks
si5351a_block(vcc3v3, gnd, i2c_sda, i2c_scl, clk0, clk1, clk2, xa, xb)
crystal_block(gnd, xa, xb)
power_block(vcc5v, vcc3v3, gnd)
connector_block(vcc5v, vcc3v3, gnd, i2c_sda, i2c_scl, clk0, clk1, clk2)

EDA_FLOORPLAN = {
    "outline": {"width_mm": 75, "height_mm": 55, "corner_radius_mm": 2.0},
}
